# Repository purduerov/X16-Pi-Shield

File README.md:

# Readme for X16-Pi-Shield
This board powers the Raspberry Pi and connects sensors to the Pi

Whenever you make a new part, download the datasheet and save it here _**and**_ with the part in the parts library

Always pull other people's changes before beginning to work
`git pull`

Be sure to push your changes after  working on them. Run:
1. `git add .` to add any files in this directory or a subdirectory
or `git add -u` to add any modified files
2. (Optional) `git clean -nX` to see what ignored files can be removed
	`git clean -fX` removes ignored files (Eagle backups)
3. `git commit -m "helpful commit message"` with a description of the work that you did
4. `git push` to push your work to github

Other helpful commands
* `git status` says information about modified and staged files
* `git log` shows the recent commits of the repository
* `git log filename.extension` show the recent commits for just that file
* `git checkout first-couple-letter-of-commit-id` lets you go back to a previous version
* `git checkout master` brings you back to the latest commit
* `git tag` lists the tags
* `git tag -a orderX -m "the version of the board placed for the X'th order"` tag a specific commit
* `git push --tags` needed to push tags to remote
* `git show orderX` show the commit log for the given tag
* `git checkout orderX` go back and interact with the files at the tagged commit

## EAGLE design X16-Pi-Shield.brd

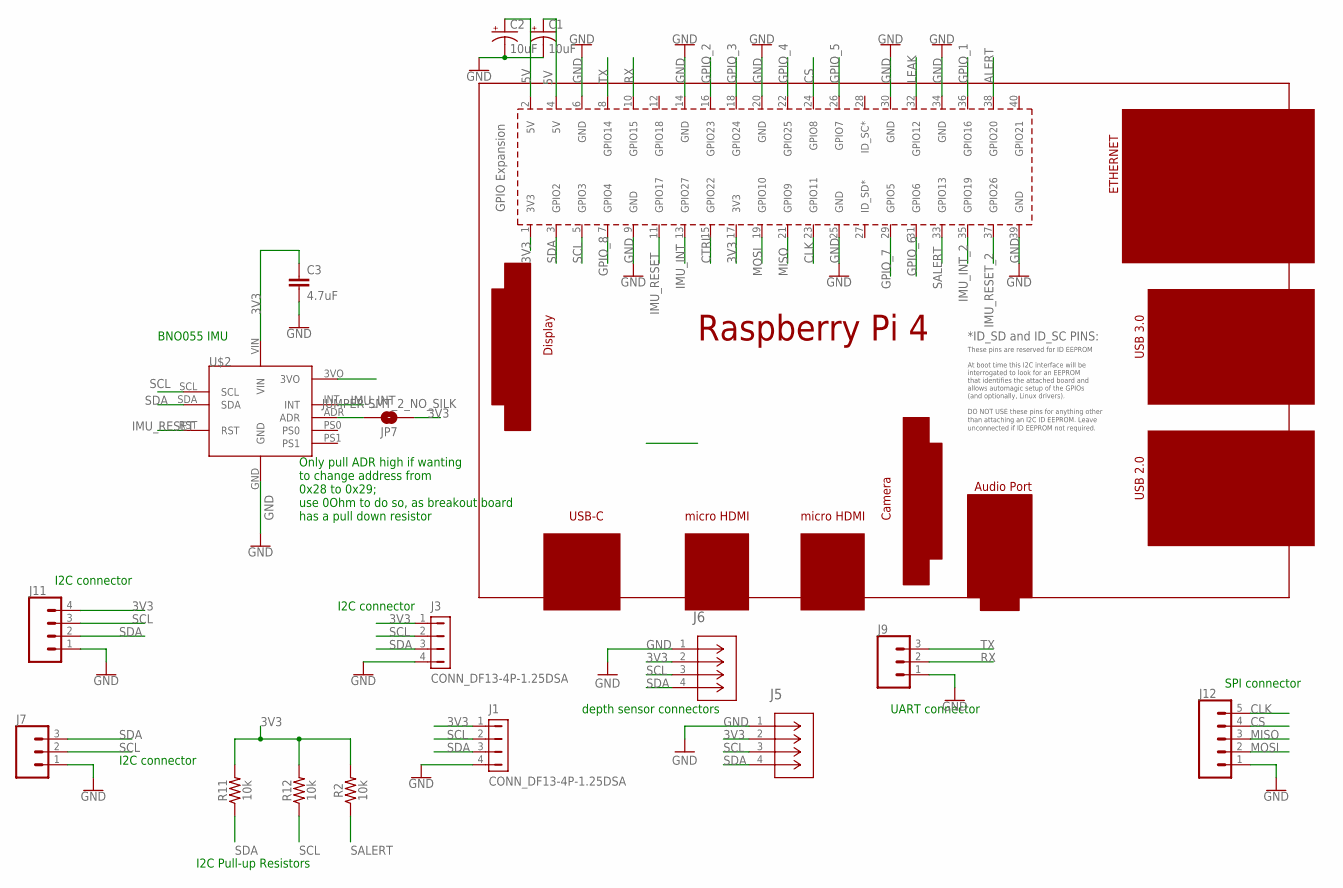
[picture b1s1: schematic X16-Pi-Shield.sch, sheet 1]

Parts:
C1, C2: 10uF; 0603-POLAR
C3: 4.7uF; 0603
J1, J3: CONN_DF13-4P-1.25DSA; DF13-4P-1.25DSA
J5, J6: BM04B-GHS-TBT; CONN_BM04B-GHS-TBT_JST
J7, J9: CONN_03; 1X03
J11: CONN_04; 1X04
J12: CONN_05; 1X05
JP7: JUMPER-SMT_2_NO_SILK; SMT-JUMPER_2_NO_SILK
R2, R11, R12: 10k; 0603
U$1: RPI4
U$2: CONN_ADAFRUIT-BNO055; ADAFRUIT-BNO055

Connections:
3V3: C3.1, J1.1, J3.1, J5.2, J6.2, J11.4, JP7.1, R2.2, R11.2, R12.2, U$1.1 (3V3), U$1.17 (3V3), U$2.VIN; also elsewhere on the board
5V: C1.+, C2.+, U$1.2 (5V), U$1.4 (5V); also elsewhere on the board
ALERT: U$1.38 (GPIO20); also elsewhere on the board
CLK: J12.5, U$1.23 (GPIO11); also elsewhere on the board
CS: J12.4, U$1.24 (GPIO8); also elsewhere on the board
CTRL: U$1.15 (GPIO22); also elsewhere on the board
GND: C1.-, C2.-, C3.2, J1.4, J3.4, J5.1, J6.1, J7.1, J9.1, J11.1, J12.1, U$1.6 (GND), U$1.9 (GND), U$1.14 (GND), U$1.20 (GND), U$1.25 (GND), U$1.30 (GND), U$1.34 (GND), U$1.39 (GND), U$2.GND; also elsewhere on the board
GPIO_1: U$1.36 (GPIO16); also elsewhere on the board
GPIO_2: U$1.16 (GPIO23); also elsewhere on the board
GPIO_3: U$1.18 (GPIO24); also elsewhere on the board
GPIO_4: U$1.22 (GPIO25); also elsewhere on the board
GPIO_5: U$1.26 (GPIO7); also elsewhere on the board
GPIO_6: U$1.31 (GPIO6); also elsewhere on the board
GPIO_7: U$1.29 (GPIO5); also elsewhere on the board
GPIO_8: U$1.7 (GPIO4); also elsewhere on the board
IMU_INT: U$1.13 (GPIO27), U$2.INT
IMU_INT_2: U$1.35 (GPIO19); also elsewhere on the board
IMU_RESET: U$1.11 (GPIO17), U$2.RST
IMU_RESET_2: U$1.37 (GPIO26); also elsewhere on the board
LEAK: U$1.32 (GPIO12); also elsewhere on the board
MISO: J12.3, U$1.21 (GPIO9); also elsewhere on the board
MOSI: J12.2, U$1.19 (GPIO10); also elsewhere on the board
unnamed: JP7.2, U$2.ADR
RX: J9.2, U$1.10 (GPIO15)
SALERT: R2.1, U$1.33 (GPIO13); also elsewhere on the board
SCL: J1.2, J3.2, J5.3, J6.3, J7.2, J11.3, R12.1, U$1.5 (GPIO3), U$2.SCL; also elsewhere on the board
SDA: J1.3, J3.3, J5.4, J6.4, J7.3, J11.2, R11.1, U$1.3 (GPIO2), U$2.SDA; also elsewhere on the board
TX: J9.3, U$1.8 (GPIO14)

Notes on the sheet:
I2C Pull-up Resistors
BNO055 IMU
Only pull ADR high if wanting to change address from 0x28 to 0x29; use 0Ohm to do so, as breakout board has a pull down resistor
I2C connector
UART connector
SPI connector
depth sensor connectors

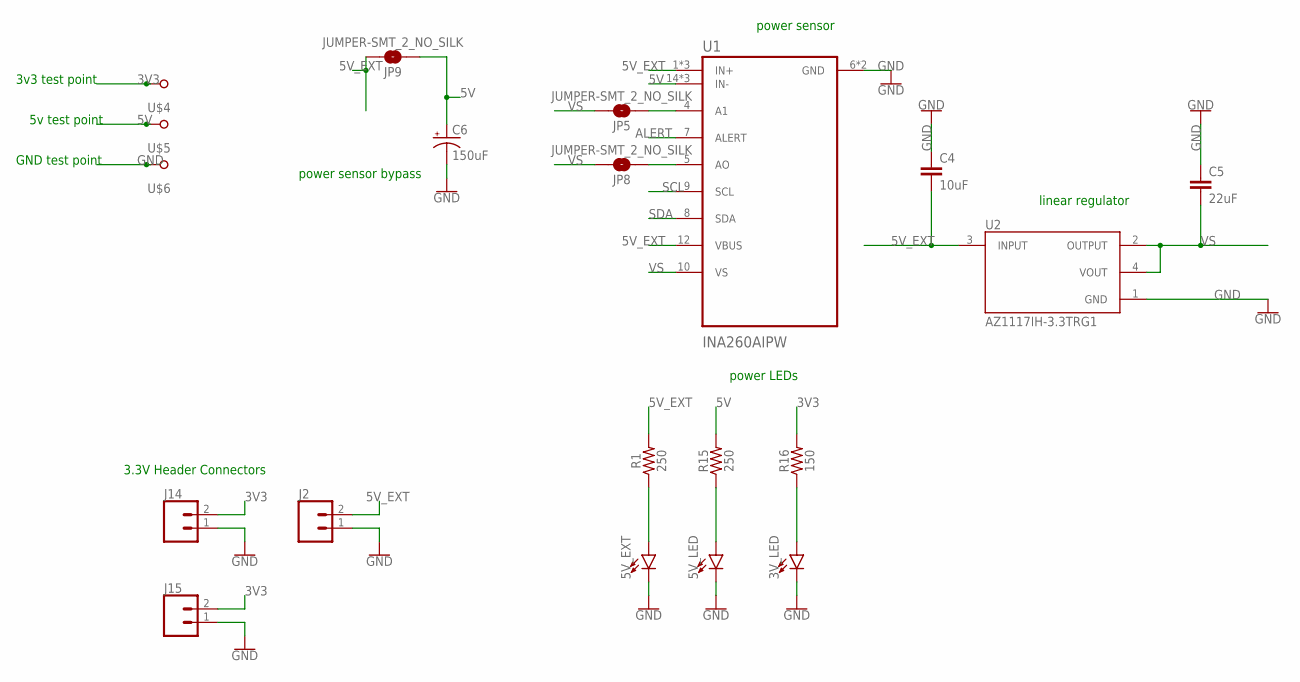
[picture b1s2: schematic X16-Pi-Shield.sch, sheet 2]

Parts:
3V_LED, 5V_EXT, 5V_LED: LEDCHIPLED_0805; CHIPLED_0805
C4: 10uF; 0603
C5: 22uF; 0603
C6: 150uF; 2917(7343-31-METRIC)
J2, J14, J15: CONN_02; 1X02
JP5, JP8, JP9: JUMPER-SMT_2_NO_SILK; SMT-JUMPER_2_NO_SILK
R1, R15: 250; 0603
R16: 150; 0603
U1: INA260AIPW; SOP65P640X120-16N
U2: AZ1117IH-3.3TRG1; SOT230P700X185-4N
U$4, U$5, U$6: TESTPOINT_5.04MM

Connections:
3V3: J14.2, J15.2, R16.2, U$4.TP; also elsewhere on the board
5V: C6.+, JP9.1, R15.2, U1.14 (IN-), U1.15 (IN-), U1.16 (IN-), U$5.TP; also elsewhere on the board
5V_EXT: C4.2, J2.2, JP9.2, R1.2, U1.1 (IN+), U1.2 (IN+), U1.3 (IN+), U1.12 (VBUS), U2.3 (INPUT); also elsewhere on the board
ALERT: U1.7 (ALERT); also elsewhere on the board
GND: 3V_LED.C, 5V_EXT.C, 5V_LED.C, C4.1, C5.1, C6.-, J2.1, J14.1, J15.1, U1.6 (GND), U1.11 (GND), U2.1 (GND), U$6.TP; also elsewhere on the board
unnamed: JP5.1, U1.4 (A1)
unnamed: JP8.1, U1.5 (AO)
unnamed: 5V_EXT.A, R1.1
unnamed: 5V_LED.A, R15.1
unnamed: 3V_LED.A, R16.1
SCL: U1.9 (SCL); also elsewhere on the board
SDA: U1.8 (SDA); also elsewhere on the board
VS: C5.2, JP5.2, JP8.2, U1.10 (VS), U2.2 (OUTPUT), U2.4 (VOUT)

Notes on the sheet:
power LEDs
3.3V Header Connectors
power sensor
linear regulator
power sensor bypass
3v3 test point
5v test point
GND test point

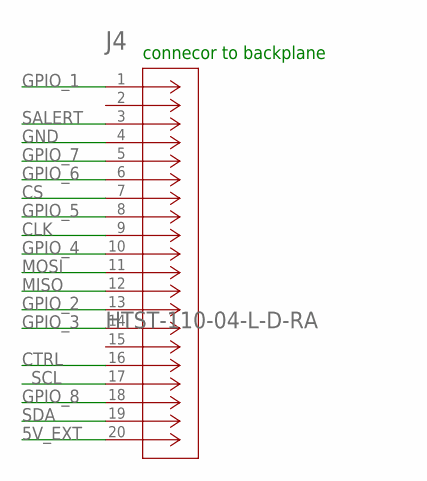
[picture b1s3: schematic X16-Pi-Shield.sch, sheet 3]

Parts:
J4: HTST-110-04-L-D-RA; CONN_HTST-110-04/05-X-D-RA_SAI

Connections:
5V_EXT: J4.20; also elsewhere on the board
CLK: J4.9; also elsewhere on the board
CS: J4.7; also elsewhere on the board
CTRL: J4.16; also elsewhere on the board
GND: J4.4; also elsewhere on the board
GPIO_1: J4.1; also elsewhere on the board
GPIO_2: J4.13; also elsewhere on the board
GPIO_3: J4.14; also elsewhere on the board
GPIO_4: J4.10; also elsewhere on the board
GPIO_5: J4.8; also elsewhere on the board
GPIO_6: J4.6; also elsewhere on the board
GPIO_7: J4.5; also elsewhere on the board
GPIO_8: J4.18; also elsewhere on the board
MISO: J4.12; also elsewhere on the board
MOSI: J4.11; also elsewhere on the board
SALERT: J4.3; also elsewhere on the board
SCL: J4.17; also elsewhere on the board
SDA: J4.19; also elsewhere on the board

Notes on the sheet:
connecor to backplane

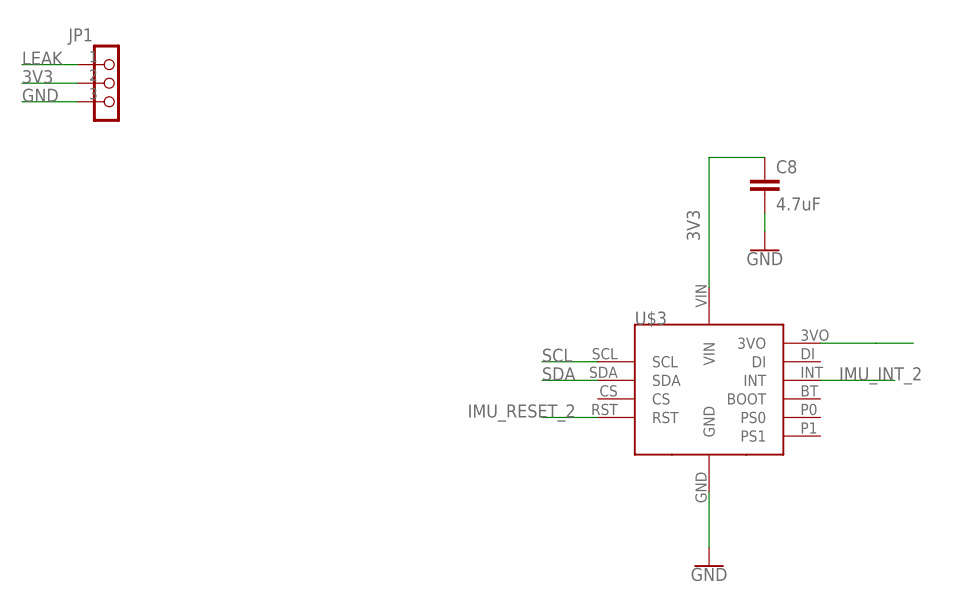
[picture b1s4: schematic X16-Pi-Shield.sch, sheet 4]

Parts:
C8: 4.7uF; 0603
JP1: TEST_PIN-1X3; 1X03
U$3: ADAFRUIT-BNO080

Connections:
3V3: C8.1, JP1.2, U$3.VIN; also elsewhere on the board
GND: C8.2, JP1.3, U$3.GND; also elsewhere on the board
IMU_INT_2: U$3.INT; also elsewhere on the board
IMU_RESET_2: U$3.RST; also elsewhere on the board
LEAK: JP1.1; also elsewhere on the board
SCL: U$3.SCL; also elsewhere on the board
SDA: U$3.SDA; also elsewhere on the board

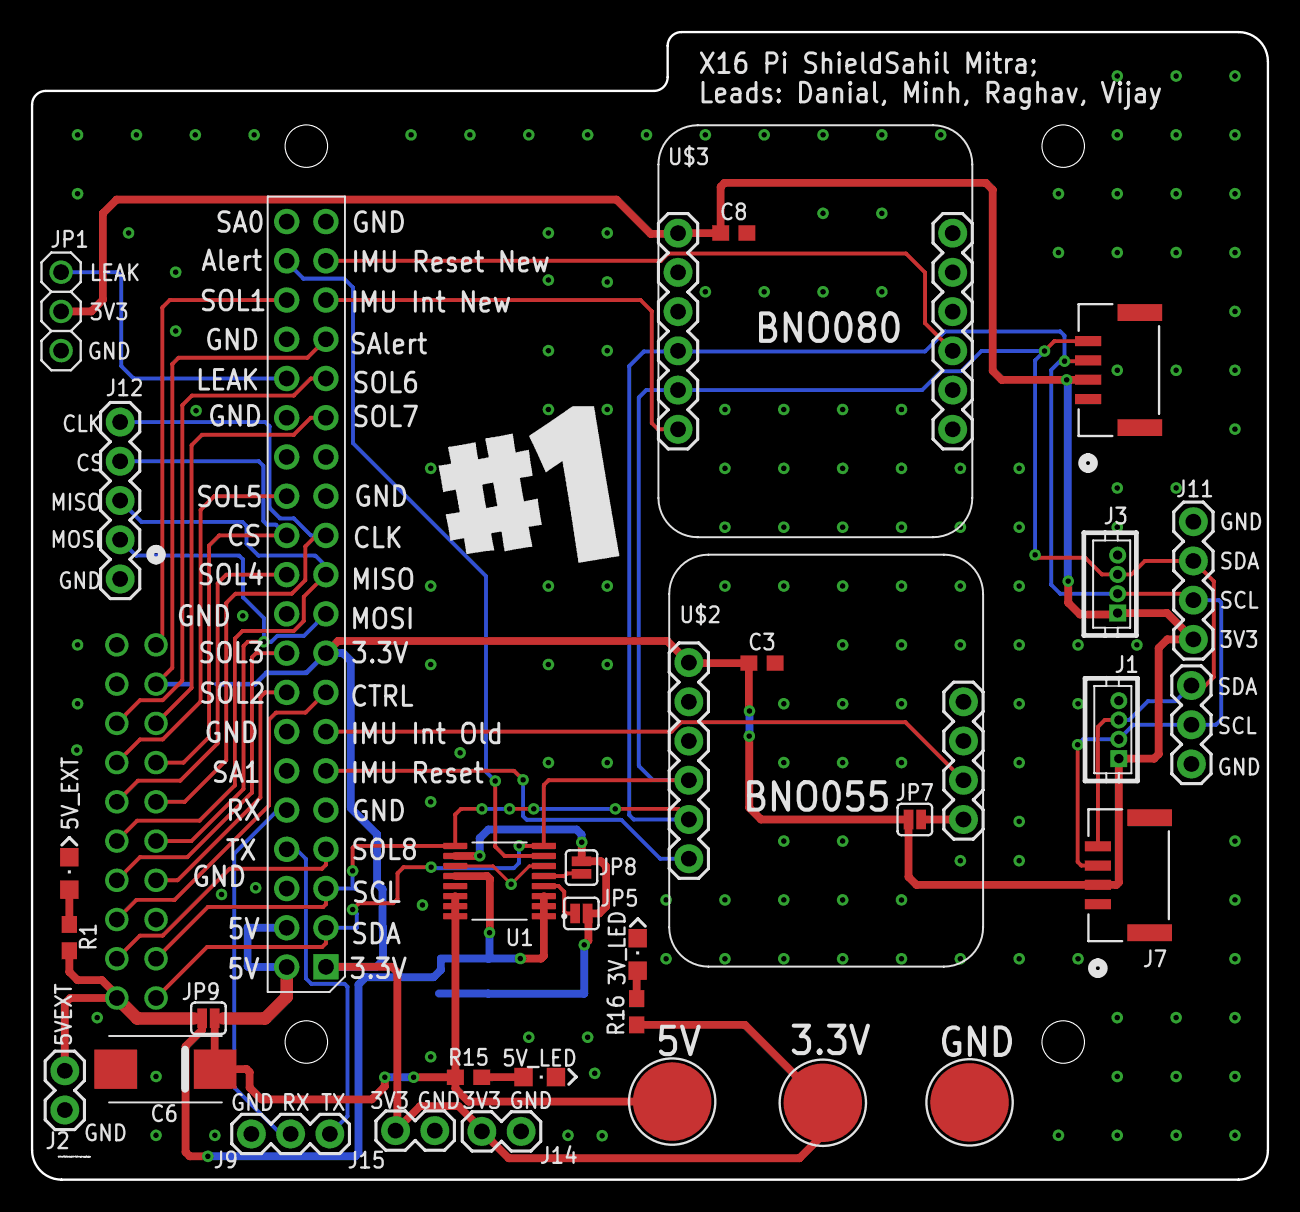
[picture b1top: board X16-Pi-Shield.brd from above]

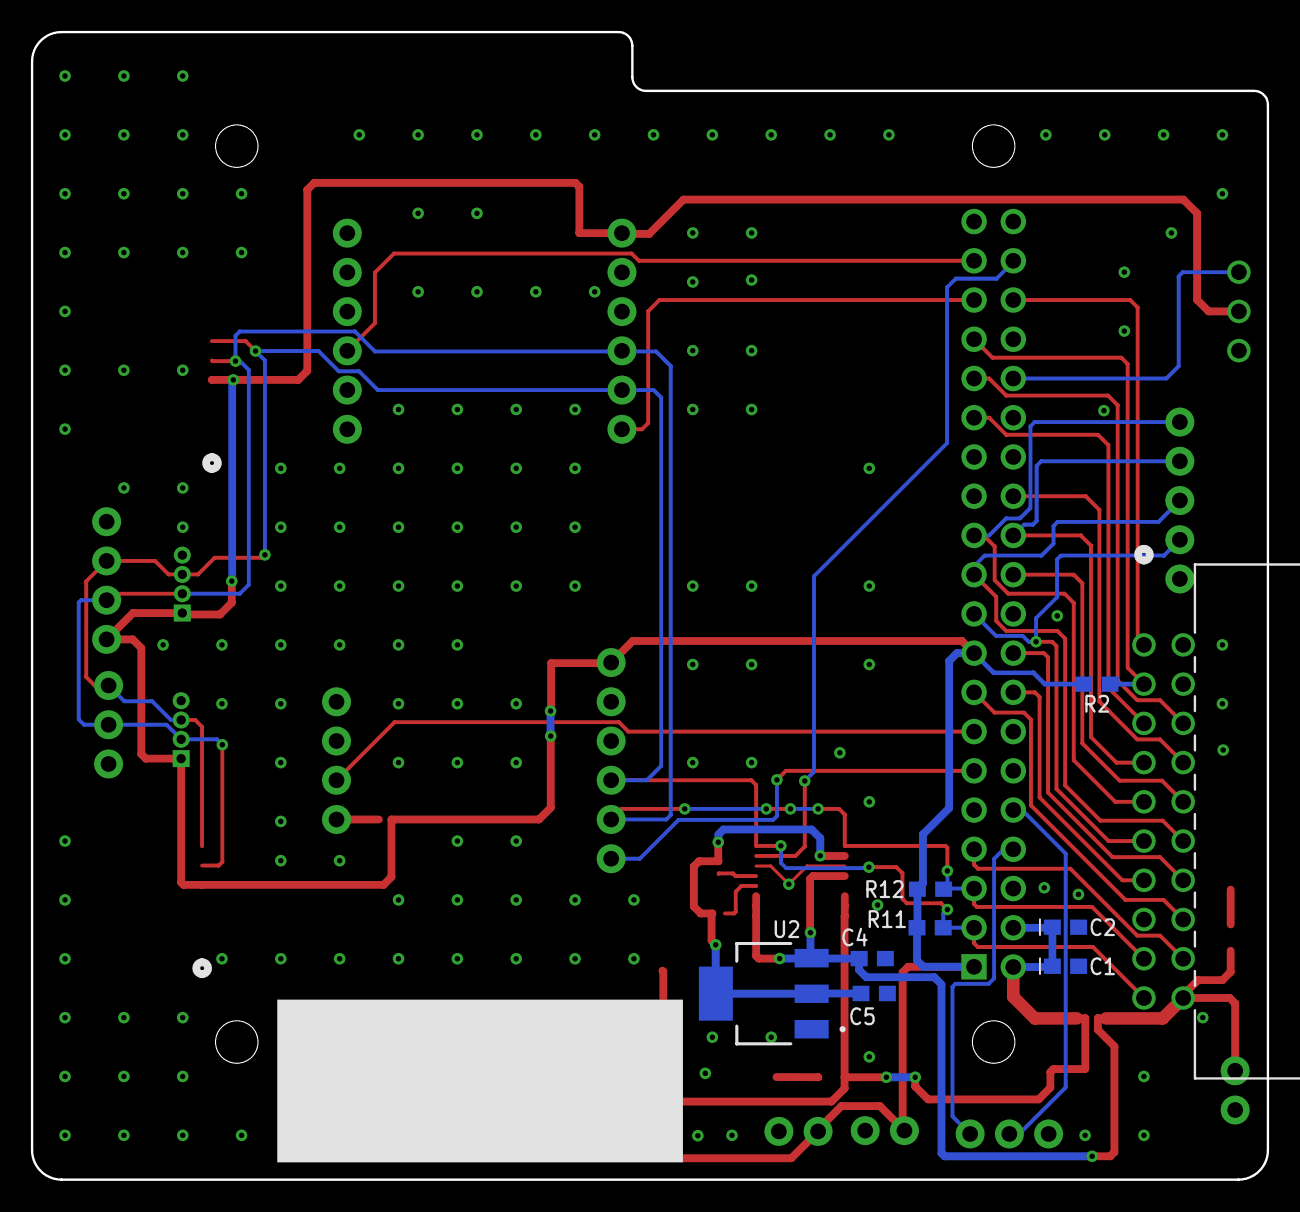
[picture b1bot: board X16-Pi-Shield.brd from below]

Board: 2 copper layers, 80.0 x 74.3 mm, 41 parts (9 on the bottom side), 35 nets.

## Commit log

2023-09-23 Init
2023-09-23 Added .gitignore file
2023-10-04 Added board dimensions
2023-10-05 finished schematic(mostly)
2023-10-11 added new board dimensions
2023-10-14 completed schematic
2023-10-14 edited schematic for new connector
2023-10-14 added connector
2023-10-14 added some nets
2023-10-14 fixed library problems
2023-10-14 made some changes
2023-10-14 updated library
2023-10-14 updated schematic and library
2023-10-18 final schematic
2023-10-21 started labeling schematic
2023-10-21 updated schematuc with labels
2023-11-04 removed unused components and added new imu
2023-11-04 added new imu
2023-11-11 updated connector footprint and connector connections
2023-11-11 routing
2023-11-11 traces
2023-11-11 more traces
2023-11-13 more
2023-11-16 stuff
2023-11-18 remade the board
2023-12-06 remade board
2023-12-08 finished board
2023-12-09 board
2023-12-09 push
2023-12-20 Minh Update
2023-12-20 Minh Update 2
2023-12-21 Added resistor values. Make sure to update BOM!
2023-12-22 Minh Update 3
2023-12-27 Revert "Minh Update 3"
    This reverts commit ef018cd753ae75237427e996904381017dc6cda3.
2023-12-27 Minh Update 4 - Edit PMBUS traces, and modify Label + Traces
2023-12-29 Minh Update 5

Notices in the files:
parts and their libraries:
SparkFun-Capacitors: Licensing: Creative Commons ShareAlike 4.0 International - https://creativecommons.org/licenses/by-sa/4.0
COPYRIGHT: Copyright (C) 2023 Ultra Librarian. All rights reserved.
